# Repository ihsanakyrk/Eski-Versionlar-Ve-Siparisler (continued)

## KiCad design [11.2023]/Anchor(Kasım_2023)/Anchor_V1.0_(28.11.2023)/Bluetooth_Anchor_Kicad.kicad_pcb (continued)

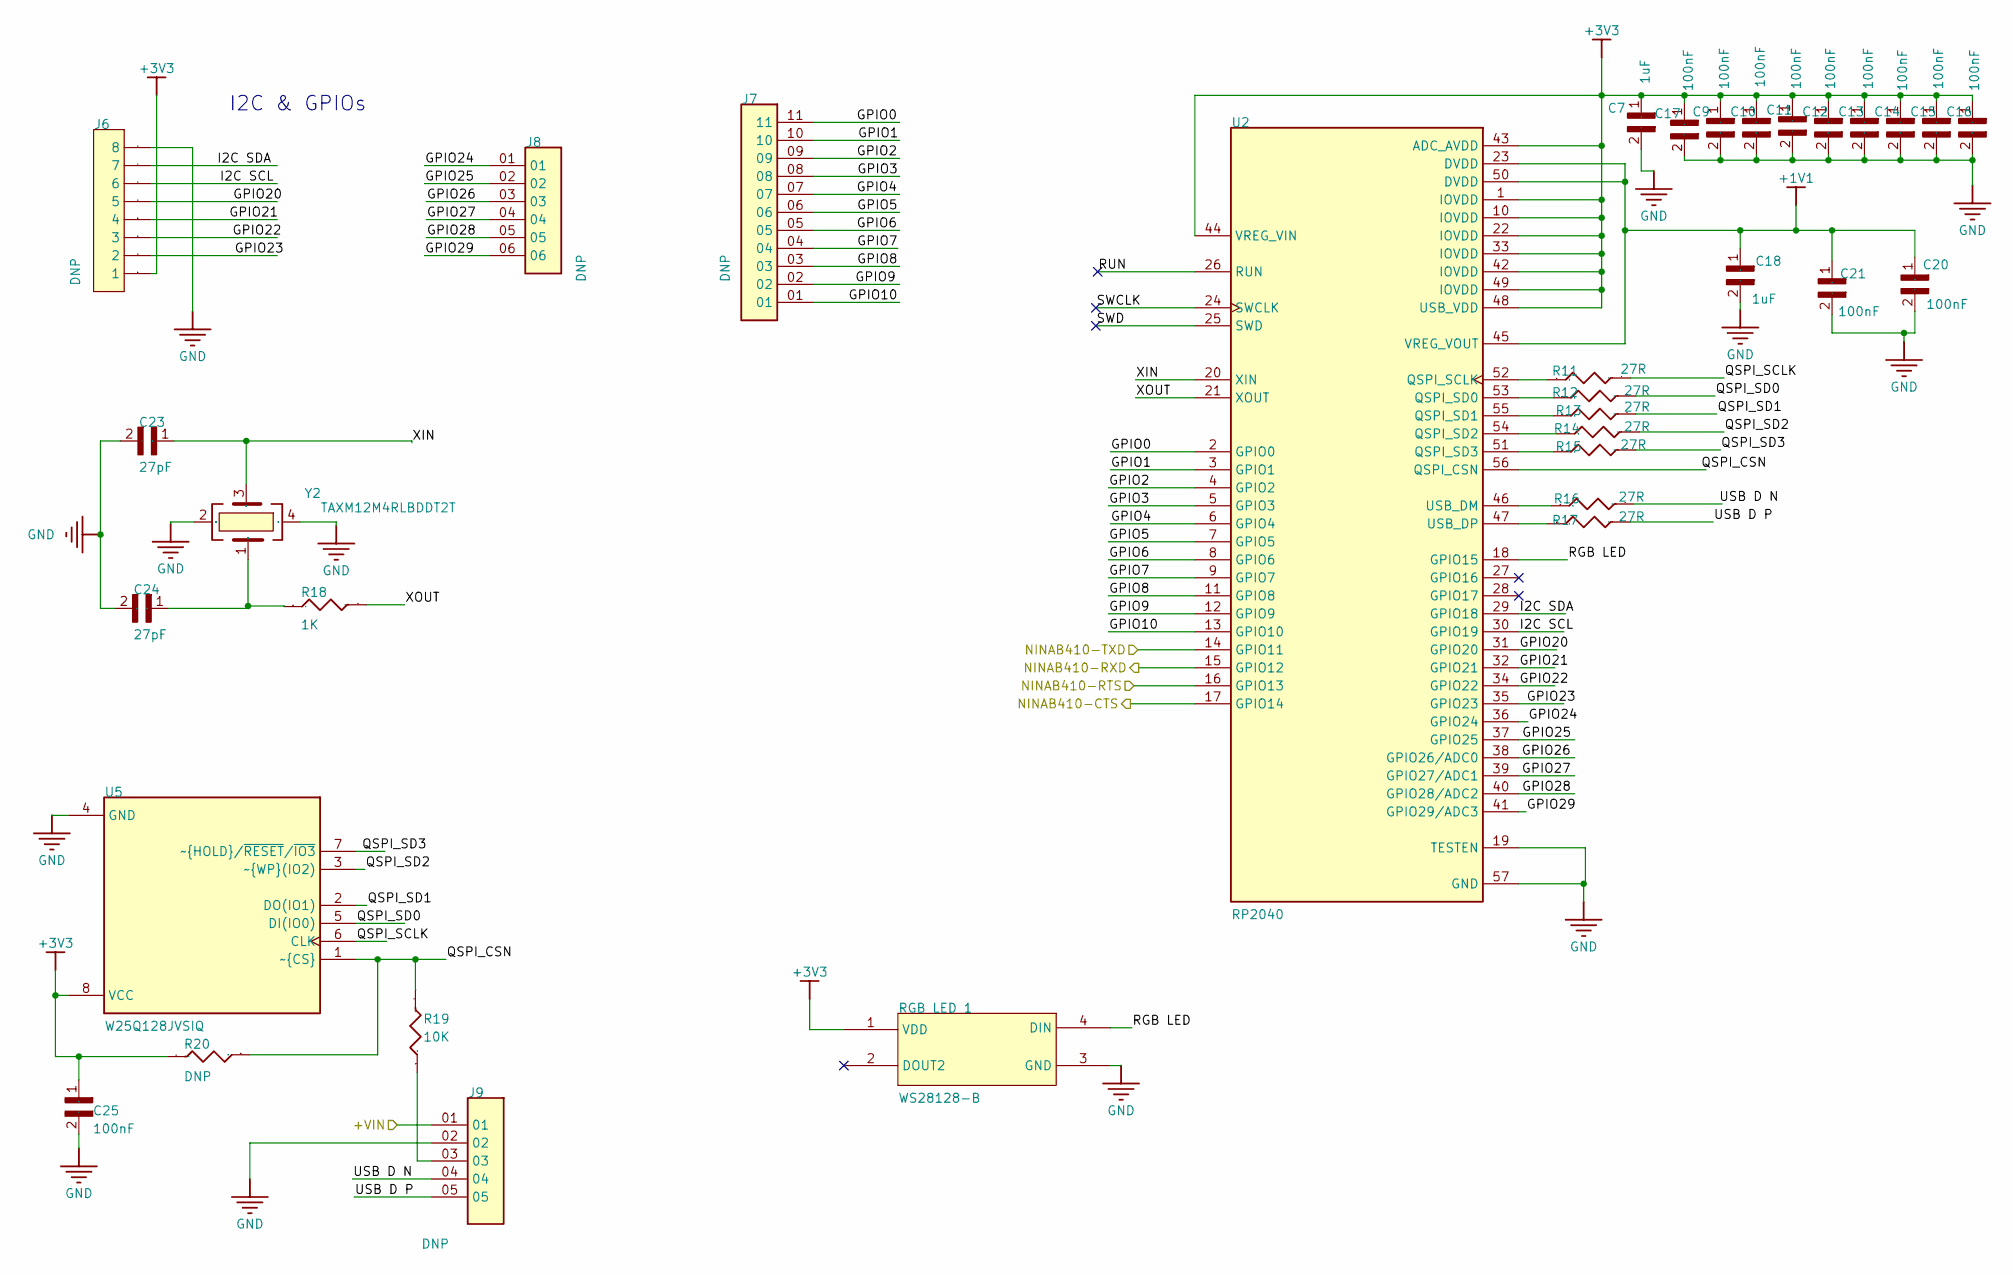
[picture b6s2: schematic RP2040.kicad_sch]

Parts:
C7, C18: 1uF; C_0402
C9, C10, C11, C12, C13, C14, C15, C16, C17, C20, C21, C25: 100nF; C_0402
C23, C24: 27pF; C_0402
J6: DNP; Header_8Ways_2x54
J7: DNP; Header 11 Ways 2x54
J8: DNP; Header_6Ways_2x54
J9: DNP; Header 5 Ways 2x54
R11, R12, R13, R14, R15, R16, R17: 27R; Res_0402
R18: 1K; Res_0402
R19: 10K; Res_0402
R20: DNP; Res_0402
RGB LED 1: WS28128-B
U2: RP2040; QFN40P700X700X90-57N
U5: W25Q128JVSIQ
Y2: TAXM12M4RLBDDT2T; Crystal_SMD_3225-4Pin_3.2x2.5mm

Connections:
+1V1: C18.1, C20.1, C21.1, U2.23 (DVDD), U2.45 (VREG_VOUT), U2.50 (DVDD)
+3V3: C7.1, C9.1, C10.1, C11.1, C12.1, C13.1, C14.1, C15.1, C16.1, C17.1, C25.1, J6.1, R20.2, RGB LED 1.1 (VDD), U2.1 (IOVDD), U2.10 (IOVDD), U2.22 (IOVDD), U2.33 (IOVDD), U2.42 (IOVDD), U2.43 (ADC_AVDD), U2.44 (VREG_VIN), U2.48 (USB_VDD), U2.49 (IOVDD), U5.8 (VCC); also elsewhere on the board
+VIN: J9.01; also elsewhere on the board
GND: C7.2, C9.2, C10.2, C11.2, C12.2, C13.2, C14.2, C15.2, C16.2, C17.2, C18.2, C20.2, C21.2, C23.2, C24.2, C25.2, J6.8, J9.02, RGB LED 1.3 (GND), U2.19 (TESTEN), U2.57 (GND), U5.4 (GND), Y2.2 (GND), Y2.4 (GND); also elsewhere on the board
GPIO0: J7.11, U2.2 (GPIO0)
GPIO1: J7.10, U2.3 (GPIO1)
GPIO2: J7.09, U2.4 (GPIO2)
GPIO3: J7.08, U2.5 (GPIO3)
GPIO4: J7.07, U2.6 (GPIO4)
GPIO5: J7.06, U2.7 (GPIO5)
GPIO6: J7.05, U2.8 (GPIO6)
GPIO7: J7.04, U2.9 (GPIO7)
GPIO8: J7.03, U2.11 (GPIO8)
GPIO9: J7.02, U2.12 (GPIO9)
GPIO10: J7.01, U2.13 (GPIO10)
GPIO20: J6.5, U2.31 (GPIO20)
GPIO21: J6.4, U2.32 (GPIO21)
GPIO22: J6.3, U2.34 (GPIO22)
GPIO23: J6.2, U2.35 (GPIO23)
GPIO24: J8.01, U2.36 (GPIO24)
GPIO25: J8.02, U2.37 (GPIO25)
GPIO26: J8.03, U2.38 (GPIO26/ADC0)
GPIO27: J8.04, U2.39 (GPIO27/ADC1)
GPIO28: J8.05, U2.40 (GPIO28/ADC2)
GPIO29: J8.06, U2.41 (GPIO29/ADC3)
I2C SCL: J6.6, U2.30 (GPIO19)
I2C SDA: J6.7, U2.29 (GPIO18)
NINAB401-RTS: U2.16 (GPIO13); also elsewhere on the board
NINAB410-CTS: U2.17 (GPIO14); also elsewhere on the board
NetC24_1: C24.1, R18.1, Y2.1 (XOUT)
NetJ9_03: J9.03, R19.1
NetR11_1: R11.1, U2.52 (QSPI_SCLK)
NetR12_1: R12.1, U2.53 (QSPI_SD0)
NetR13_1: R13.1, U2.55 (QSPI_SD1)
NetR14_1: R14.1, U2.54 (QSPI_SD2)
NetR15_1: R15.1, U2.51 (QSPI_SD3)
NetR16_1: R16.1, U2.46 (USB_DM)
NetR17_1: R17.1, U2.47 (USB_DP)
QSPI_CSN: R19.2, R20.1, U2.56 (QSPI_CSN), U5.1 (~CS~{})
QSPI_SCLK: R11.2, U5.6 (CLK)
QSPI_SD0: R12.2, U5.5 (DI(IO0))
QSPI_SD1: R13.2, U5.2 (DO(IO1))
QSPI_SD2: R14.2, U5.3 (~WP~{}(IO2))
QSPI_SD3: R15.2, U5.7 (~HOLD~{}/~RESET/~IO3)
RGB LED: RGB LED 1.4 (DIN), U2.18 (GPIO15)
RUN: U2.26 (RUN)
RXD: U2.15 (GPIO12); also elsewhere on the board
SWCLK: U2.24 (SWCLK)
SWD: U2.25 (SWD)
TXD: U2.14 (GPIO11); also elsewhere on the board
USB D N: J9.04, R16.2
USB D P: J9.05, R17.2
XIN: C23.1, U2.20 (XIN), Y2.3 (XIN)
XOUT: R18.2, U2.21 (XOUT)

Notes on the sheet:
I2C & GPIOs

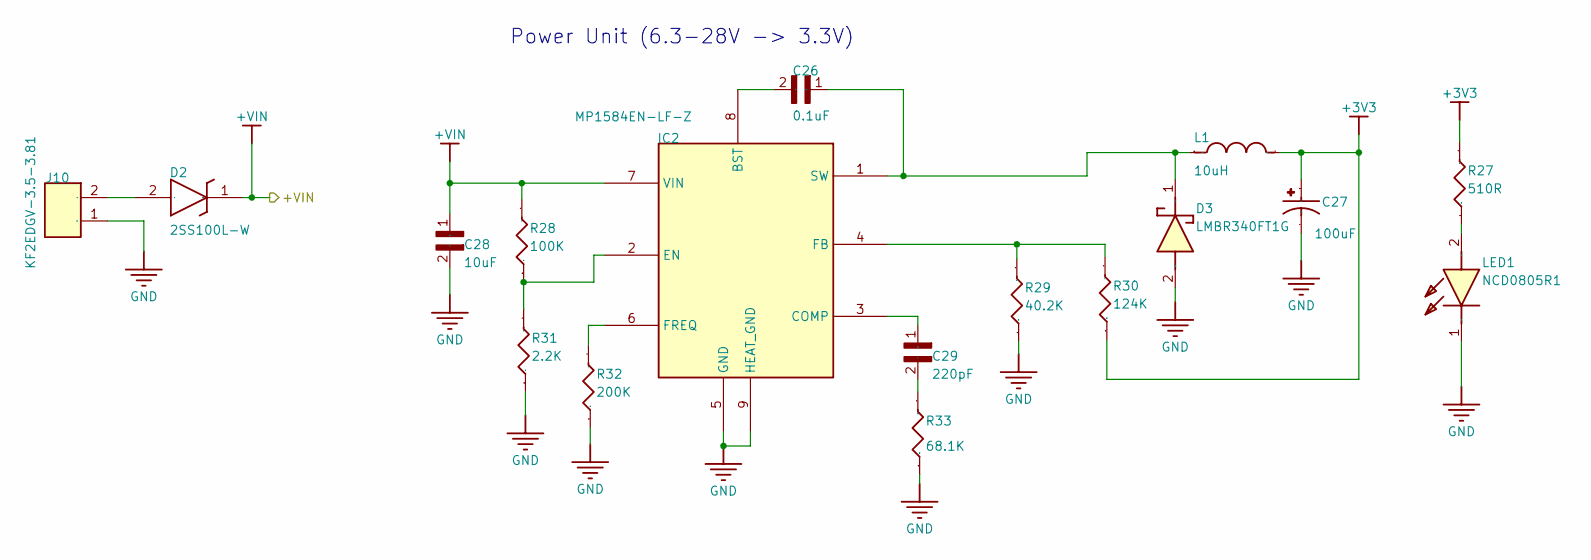
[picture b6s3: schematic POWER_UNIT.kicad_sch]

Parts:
C26: 0.1uF; C_0402
C27: 100uF; XT100UF10V90RV0060
C28: 10uF; C_0402
C29: 220pF; C_0402
D2: 2SS100L-W; 2SS100LW; MANUFACTURER_PART_NUMBER 2SS100L-W; MOUSER PART NUMBER 583-2SS100L-W
D3: LMBR340FT1G; SODFL3618X143N; MANUFACTURER_PART_NUMBER SS34FA; MOUSER PART NUMBER 512-SS34FA
IC2: MP1584EN-LF-Z; SOIC127P600X170-9N
J10: KF2EDGV-3.5-3.81; SHDR2W80P0X381_1X2_862X700X920P
L1: 10uH; YSPI0530-100M
LED1: NCD0805R1; MANUFACTURER_PART_NUMBER NCD0805R1; MOUSER PART NUMBER *
R27: 510R; Res_0402
R28: 100K; Res_0402
R29: 40.2K; Res_0402
R30: 124K; Res_0402
R31: 2.2K; Res_0402
R32: 200K; Res_0402
R33: 68.1K; Res_0402

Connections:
+3V3: C27.1, L1.2, R27.2, R30.1; also elsewhere on the board
+VIN: C28.1, D2.1 (K), IC2.7 (VIN), R28.2; also elsewhere on the board
GND: C27.2, C28.2, D3.2 (A), IC2.5 (GND), IC2.9 (HEAT_GND), J10.1, LED1.1 (K), R29.1, R31.1, R32.1, R33.1; also elsewhere on the board
NetC26_1: C26.1, D3.1 (K), IC2.1 (SW), L1.1
NetC26_2: C26.2, IC2.8 (BST)
NetC29_1: C29.1, IC2.3 (COMP)
NetC29_2: C29.2, R33.2
NetD2_2: D2.2 (A), J10.2
NetD4_2: LED1.2 (A), R27.1
NetR28_1: IC2.2 (EN), R28.1, R31.2
NetR29_2: IC2.4 (FB), R29.2, R30.2
NetR32_2: IC2.6 (FREQ), R32.2

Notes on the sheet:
Power Unit (6.3-28V -> 3.3V)

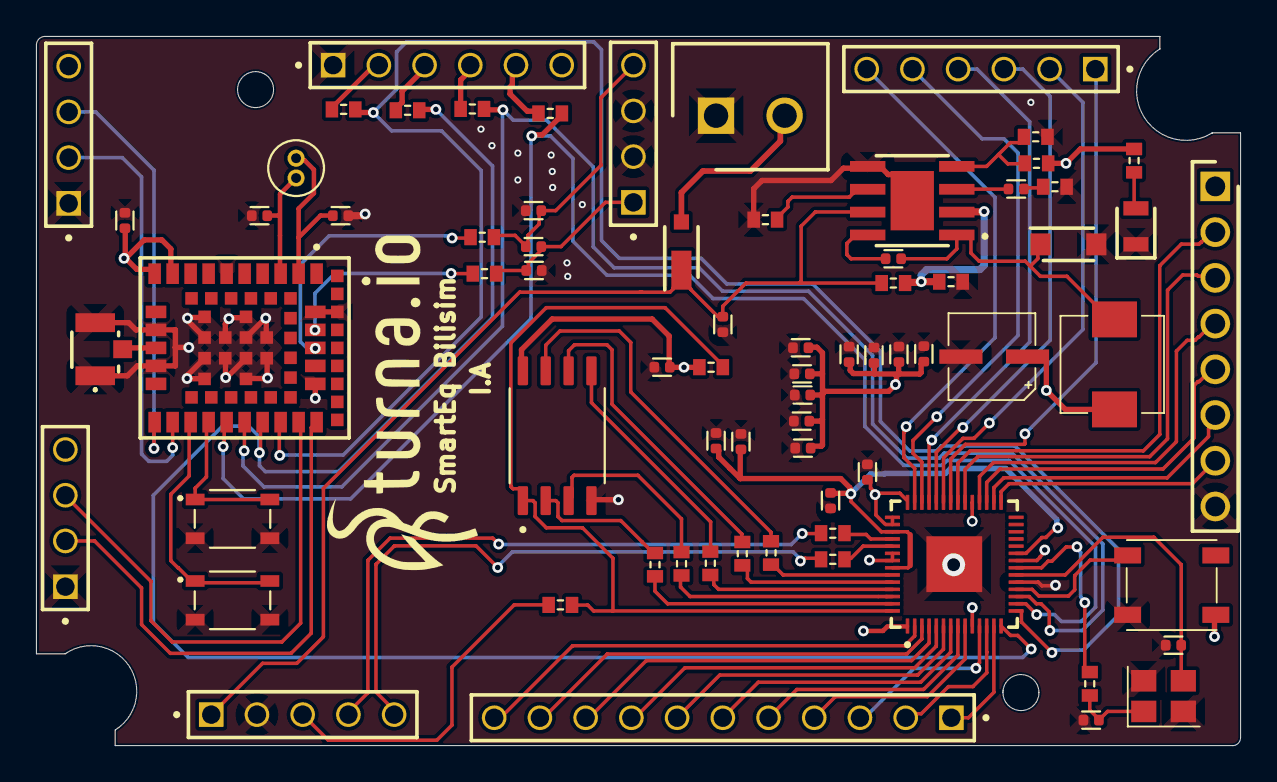
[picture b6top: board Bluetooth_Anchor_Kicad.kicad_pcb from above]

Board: 4 copper layers, 66.9 x 39.4 mm, 72 parts (0 on the bottom side), 77 nets.

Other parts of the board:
C5: DNP; C_0402

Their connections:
NetC4_2: C5.1; also elsewhere on the board
NetC6_1: C5.2; also elsewhere on the board

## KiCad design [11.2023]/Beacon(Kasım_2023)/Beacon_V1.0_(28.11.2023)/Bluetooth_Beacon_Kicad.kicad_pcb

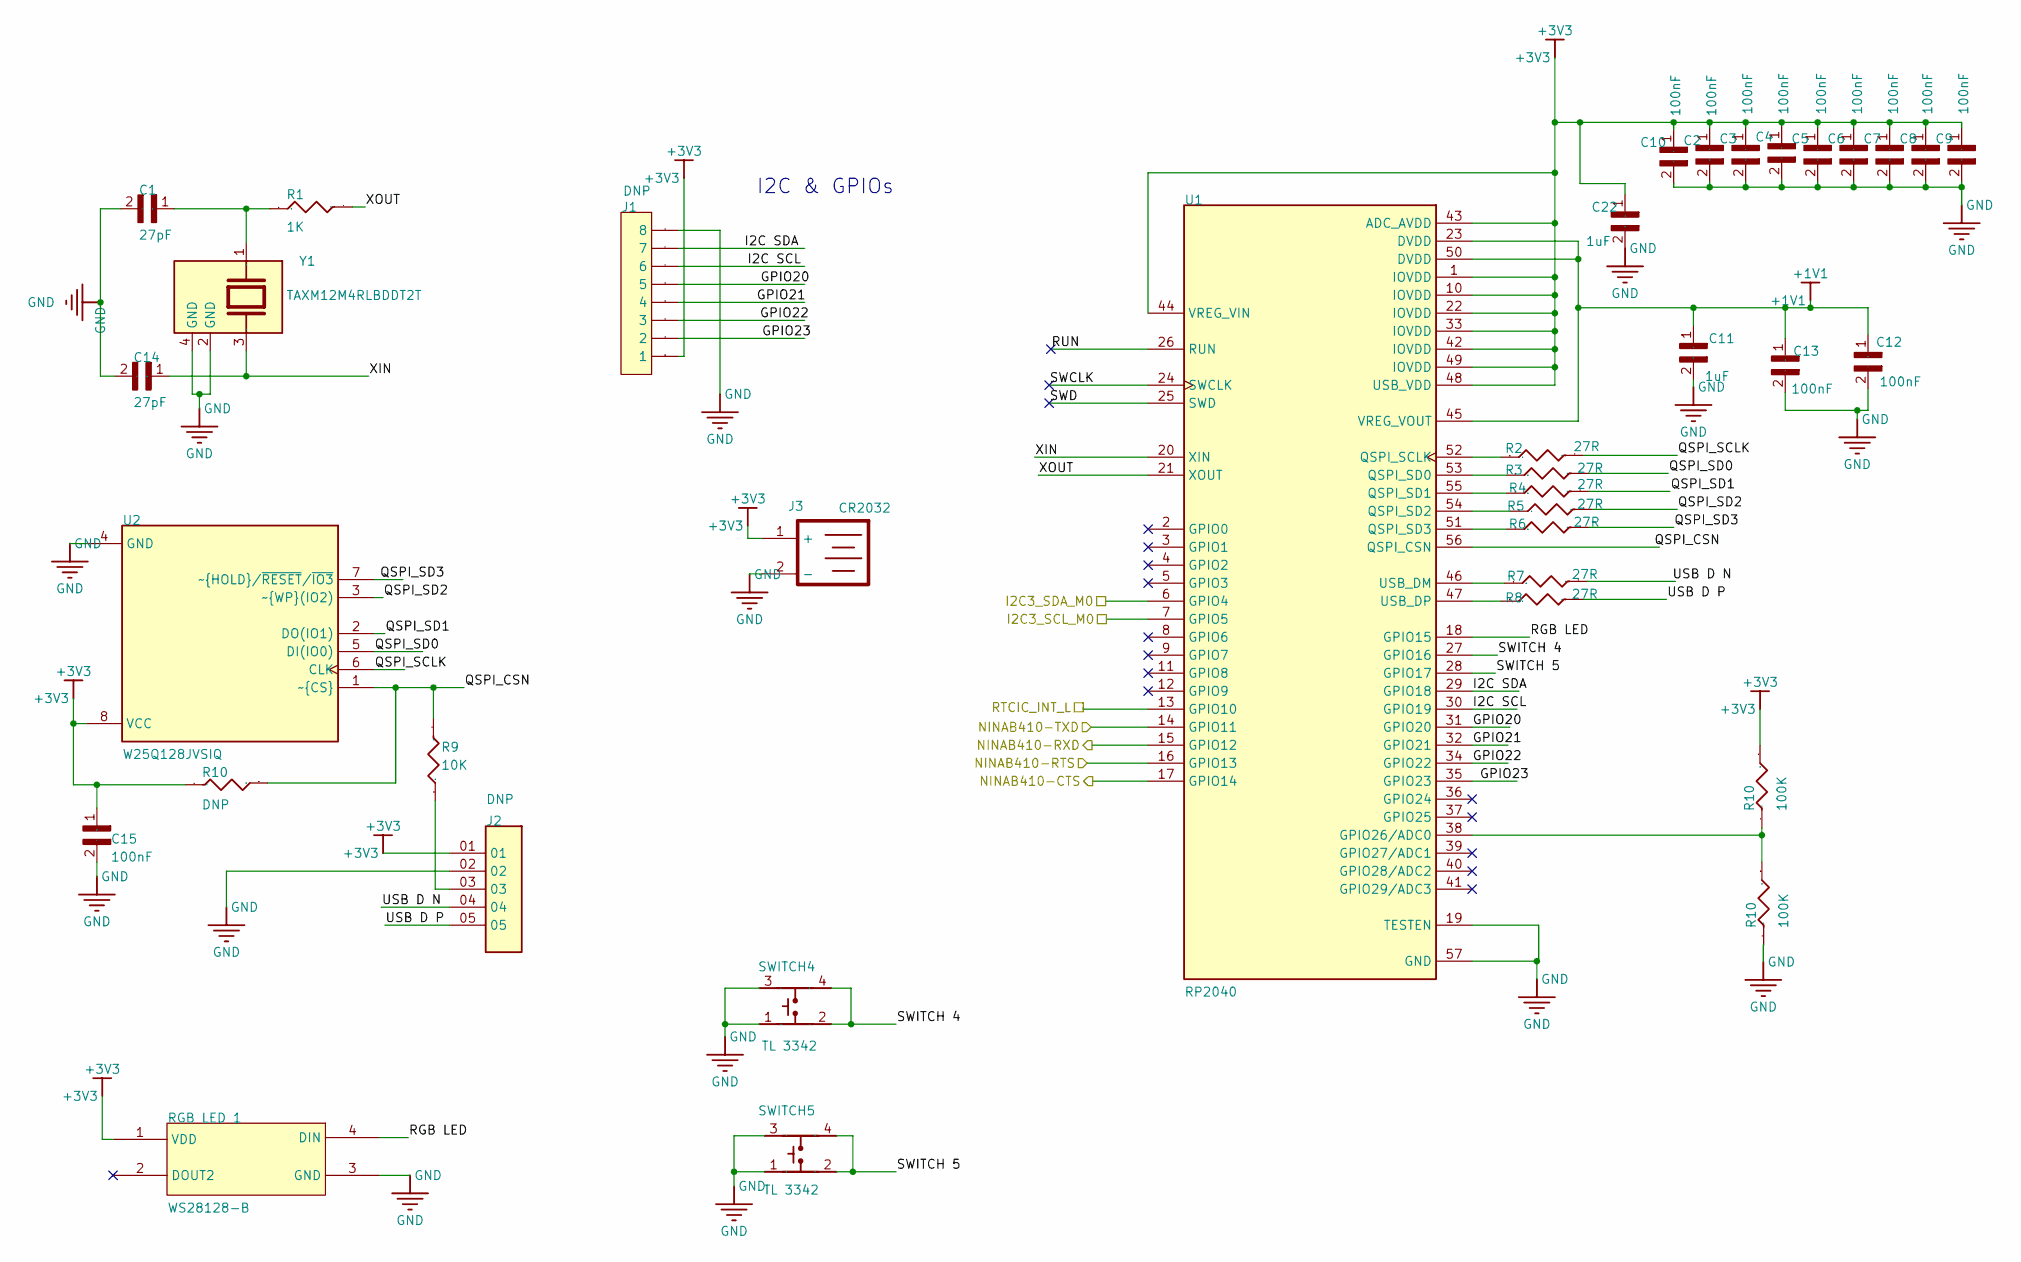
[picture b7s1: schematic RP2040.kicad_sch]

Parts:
C1, C14: 27pF; C_0402
C2, C3, C4, C5, C6, C7, C8, C9, C12, C13: 100nF; c_0402
C10: 100nF; CAPC1005X55N
C11, C22: 1uF; c_0402
C15: 100nF; C_0402
J1: DNP; Header_8Ways_2x54
J2: DNP; Header 5 Ways 2x54
J3: CR2032; Coin Cell Battery Holder
R1: 1K; Res_0402
R2, R3, R4, R5, R6, R7, R8: 27R; Res_0402
R9: 10K; Res_0402
R10: 100K; R_0402_1005Metric
RGB LED 1: WS28128-B
SWITCH4, SWITCH5: TL 3342
U1: RP2040; QFN40P700X700X90-57N
U2: W25Q128JVSIQ
Y1: TAXM12M4RLBDDT2T; Crystal_SMD_3225-4Pin_3.2x2.5mm

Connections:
+1V1: C11.1, C12.1, C13.1, U1.23 (DVDD), U1.45 (VREG_VOUT), U1.50 (DVDD)
GPIO20: J1.5, U1.31 (GPIO20)
GPIO21: J1.4, U1.32 (GPIO21)
GPIO22: J1.3, U1.34 (GPIO22)
GPIO23: J1.2, U1.35 (GPIO23)
I2C SCL: J1.6, U1.30 (GPIO19)
I2C SDA: J1.7, U1.29 (GPIO18)
NINAB401-RTS: U1.16 (GPIO13); also elsewhere on the board
NINAB410-CTS: U1.17 (GPIO14); also elsewhere on the board
NetC1_1: C1.1, R1.1, Y1.1
NetJ2_03: J2.03, R9.1
NetR2_1: R2.1, U1.52 (QSPI_SCLK)
NetR3_1: R3.1, U1.53 (QSPI_SD0)
NetR4_1: R4.1, U1.55 (QSPI_SD1)
NetR5_1: R5.1, U1.54 (QSPI_SD2)
NetR6_1: R6.1, U1.51 (QSPI_SD3)
NetR7_1: R7.1, U1.46 (USB_DM)
NetR8_1: R8.1, U1.47 (USB_DP)
NetR15_1: U1.13 (GPIO10); also elsewhere on the board
NetR16_2: U1.6 (GPIO4); also elsewhere on the board
NetR17_2: U1.7 (GPIO5); also elsewhere on the board
NetR20_1: U1.39 (GPIO27/ADC1); also elsewhere on the board
QSPI_SCLK: R2.2, U2.6 (CLK)
QSPI_SD0: R3.2, U2.5 (DI(IO0))
QSPI_SD1: R4.2, U2.2 (DO(IO1))
QSPI_SD2: R5.2, U2.3 (~WP~{}(IO2))
QSPI_SD3: R6.2, U2.7 (~HOLD~{}/~RESET/~IO3)
RGB LED: RGB LED 1.4 (DIN), U1.18 (GPIO15)
RUN: U1.26 (RUN)
RXD: U1.15 (GPIO12); also elsewhere on the board
SWCLK: U1.24 (SWCLK)
SWD: U1.25 (SWD)
SWITCH 4: SWITCH4.2, SWITCH4.4, U1.27 (GPIO16)
SWITCH 5: SWITCH5.2, SWITCH5.4, U1.28 (GPIO17)
TXD: U1.14 (GPIO11); also elsewhere on the board
USB D N: J2.04, R7.2
USB D P: J2.05, R8.2
XIN: C14.1, U1.20 (XIN), Y1.3 (2)
XOUT: R1.2, U1.21 (XOUT)

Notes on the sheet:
I2C & GPIOs

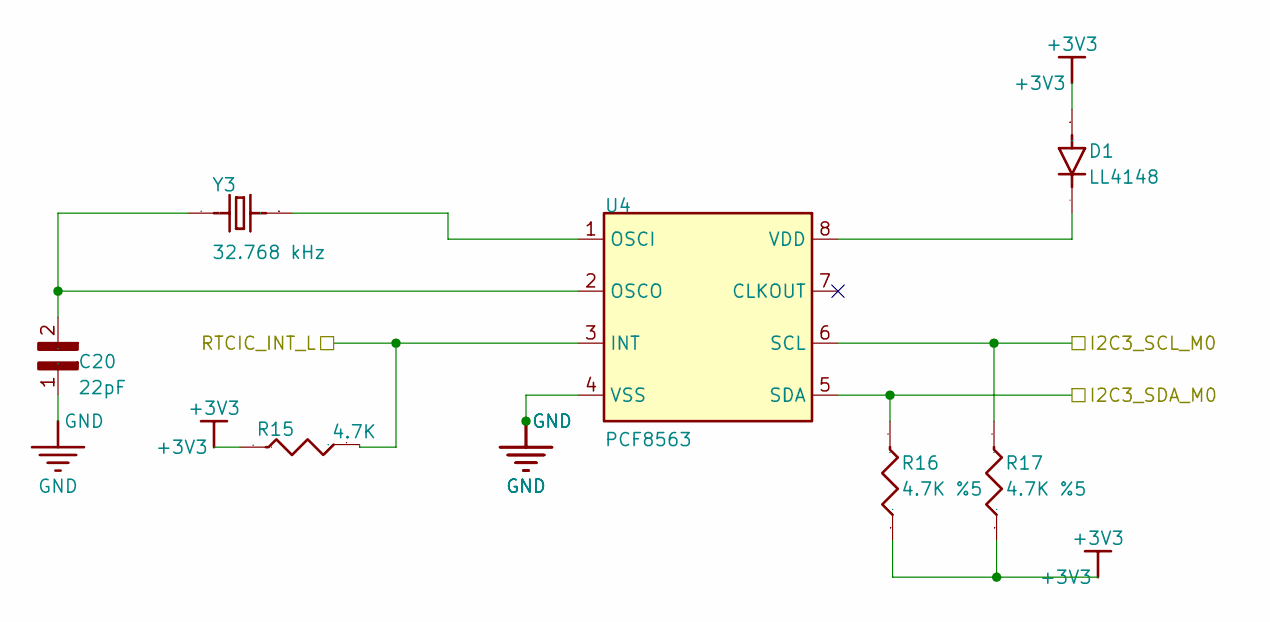
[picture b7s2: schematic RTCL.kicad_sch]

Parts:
C20: 22pF; c_0402
D1: LL4148; DIO_LL4148
R15: 4.7K; Res_0402
R16, R17: 4.7K %5; Res_0402
U4: PCF8563
Y3: 32.768 kHz; XTAL_ECS-3X8X

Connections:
NetC20_2: C20.2, U4.2 (OSCO), Y3.2
NetD1_C: D1.C, U4.8 (VDD)
NetR15_1: R15.1, U4.3 (INT); also elsewhere on the board
NetR16_2: R16.2, U4.5 (SDA); also elsewhere on the board
NetR17_2: R17.2, U4.6 (SCL); also elsewhere on the board
NetU4_1: U4.1 (OSCI), Y3.1

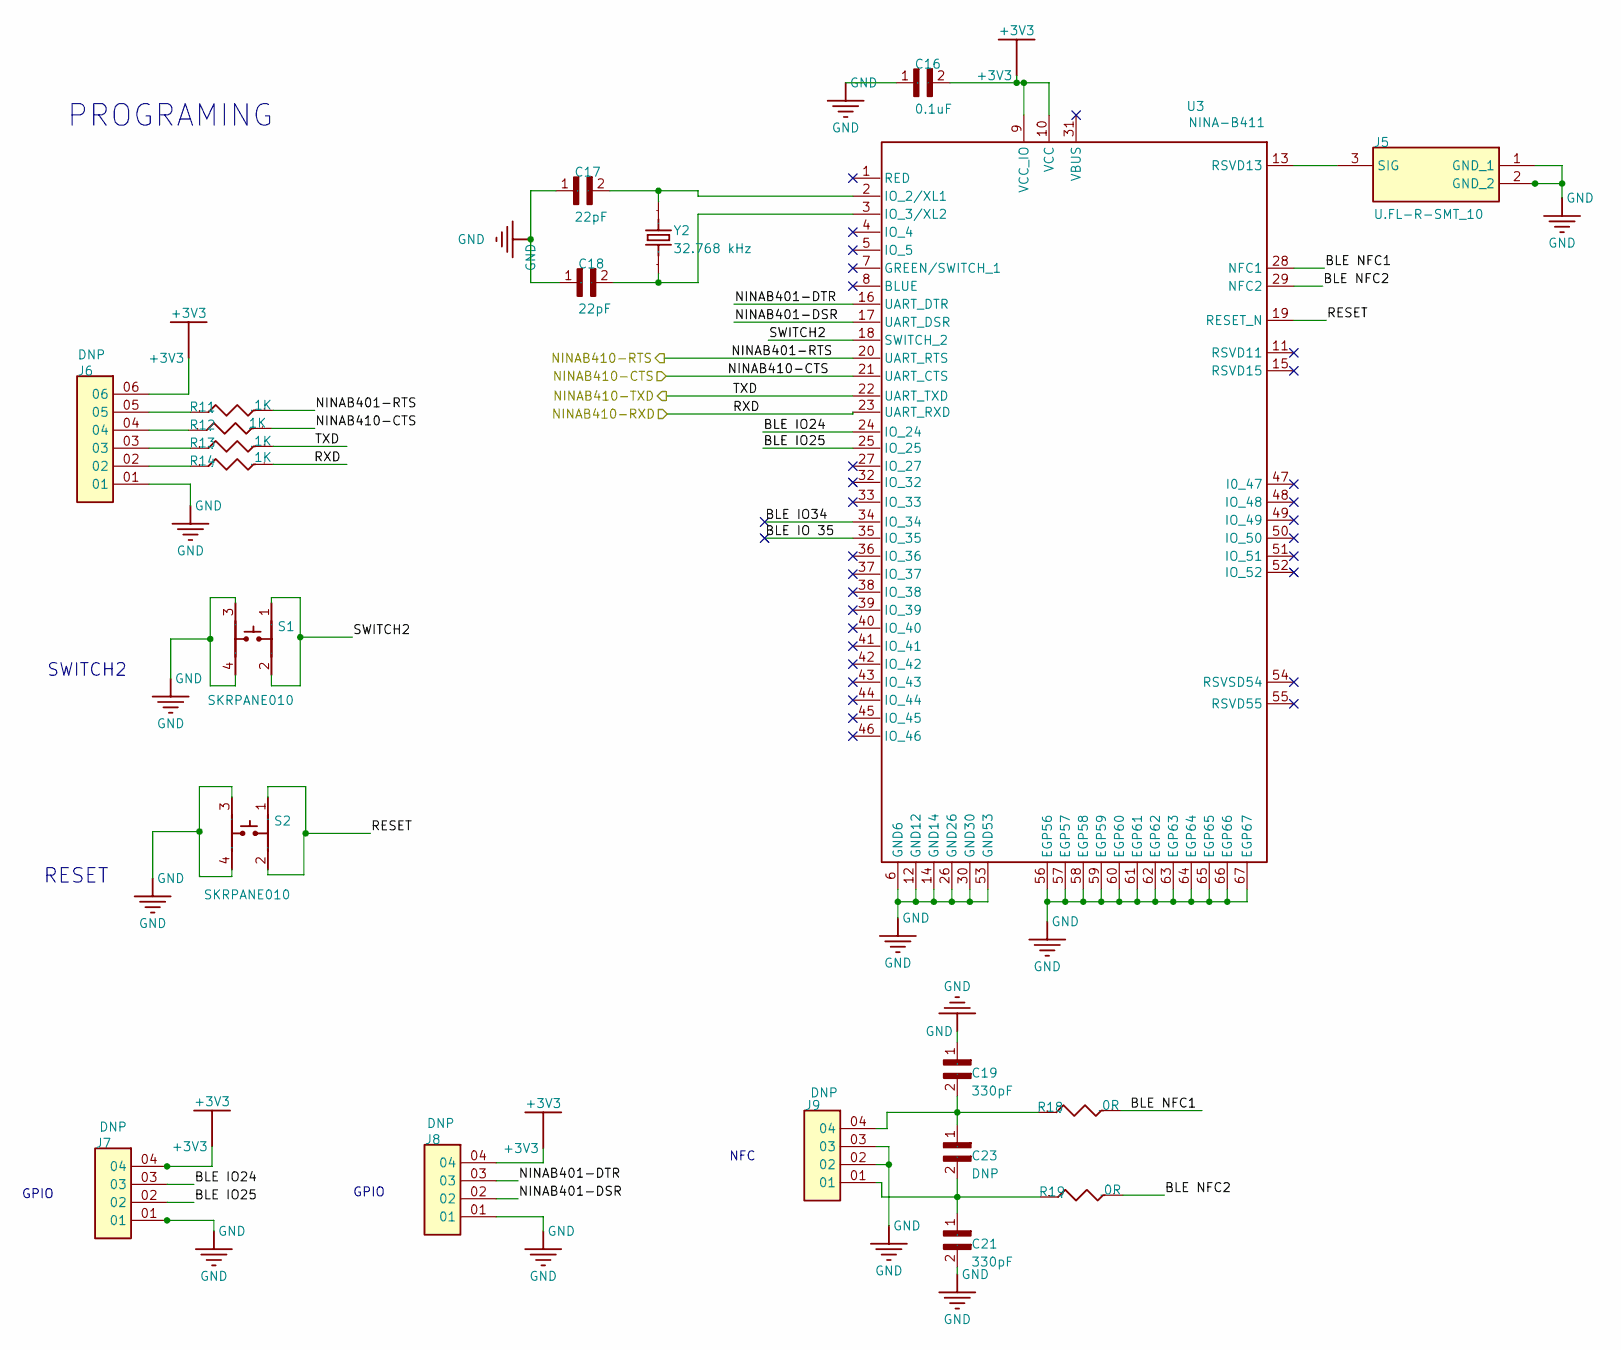
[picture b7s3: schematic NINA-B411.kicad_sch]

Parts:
C16: 0.1uF; C_0402
C17, C18: 22pF; C_0402
C19, C21: 330pF; C_0402
C23: DNP; C_0402
J5: U.FL-R-SMT_10; UFLRSMT10; MANUFACTURER_PART_NUMBER U.FL-R-SMT(10); MOUSER PART NUMBER 798-U.FL-R-SMT10
J6: DNP; Header_6Ways_2x54
J7, J8, J9: DNP; Header_4Ways_2x54_Male
R11, R12, R13, R14: 1K; Res_0402
R18, R19: 0R; Res_0402
S1, S2: SKRPANE010
U3: NINA-B411; NINA_LGA67R_1160X1000X223_PIN - duplicate
Y2: 32.768 kHz; XTAL_ECS-3X8X

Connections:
BLE IO24: J7.03, U3.24 (IO_24)
BLE IO25: J7.02, U3.25 (IO_25)
BLE IO34: U3.34 (IO_34)
BLE IO 35: U3.35 (IO_35)
BLE NFC1: R18.2, U3.28 (NFC1)
BLE NFC2: R19.2, U3.29 (NFC2)
NINAB401-DSR: J8.02, U3.17 (UART_DSR)
NINAB401-DTR: J8.03, U3.16 (UART_DTR)
NINAB401-RTS: R11.2, U3.20 (UART_RTS); also elsewhere on the board
NINAB410-CTS: R12.2, U3.21 (UART_CTS); also elsewhere on the board
NetC17_2: C17.2, U3.2 (IO_2/XL1), Y2.2
NetC18_2: C18.2, U3.3 (IO_3/XL2), Y2.1
NetC19_2: C19.2, C23.1, J9.04, R18.1
NetC21_1: C21.1, C23.2, J9.01, R19.1
NetJ5_3: J5.3 (SIG), U3.13 (RSVD13)
NetJ6_02: J6.02, R14.1
NetJ6_03: J6.03, R13.1
NetJ6_04: J6.04, R12.1
NetJ6_05: J6.05, R11.1
RESET: S2.1, S2.2, U3.19 (RESET_N)
RXD: R14.2, U3.23 (UART_RXD); also elsewhere on the board
SWITCH2: S1.1, S1.2, U3.18 (SWITCH_2)
TXD: R13.2, U3.22 (UART_TXD); also elsewhere on the board

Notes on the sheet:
NFC
GPIO
SWITCH2
PROGRAMING
RESET

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
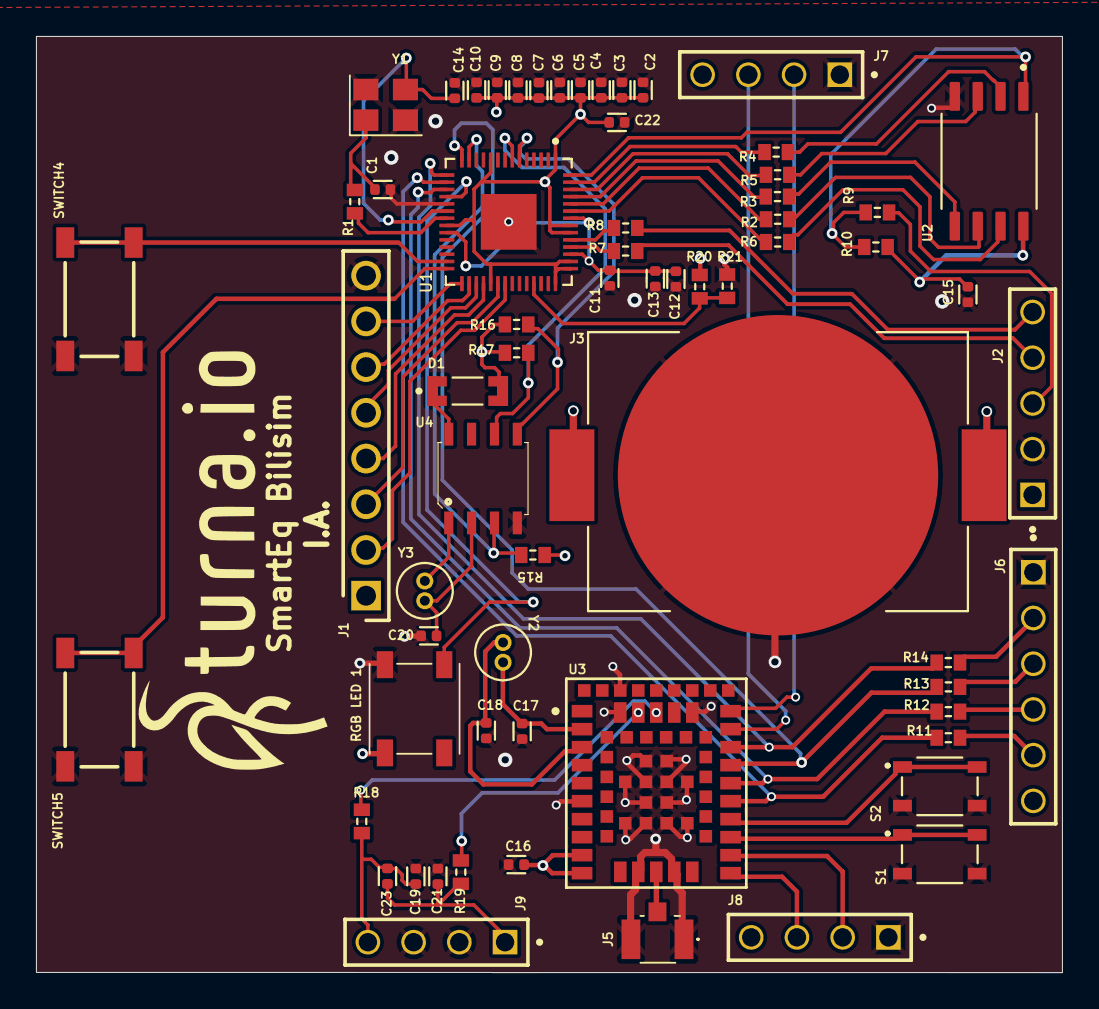
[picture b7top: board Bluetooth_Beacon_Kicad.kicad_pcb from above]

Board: 4 copper layers, 57.0 x 52.0 mm, 65 parts (0 on the bottom side), 59 nets.

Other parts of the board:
R20, R21: 100K; Res_0402

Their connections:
NetR20_1: R20.1, R21.2; also elsewhere on the board
